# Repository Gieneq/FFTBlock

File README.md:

# FFTslice

Module to evaluate FFT. Communication with SPI. PGA for gain control. 2 selectable channels, additional DAC channel for selftest.

## DAC samples generation

See [notebook](Doc/DAC_samples/FFTSlice_DAC.ipynb) with all calculations. 

Frequencies from 20 Hz to 20 kHz are splitted into 100 ranges in logspace to better fit sound perception. 

3 variables affects output DAC frequency:
- constant TIM1 clock = 64 MHz,
- variable divider
- samples count

Divider can be freely changed, but samples count have to be generated in advance and stored in FLASH. There are 6 samples counts: 64, 128, 256, 512, 1024 and 2048. Higher samples counts fits better to generate low frequencies, lower samples counts are better fot higher frequencies.

100 parameters are calculated so that samples count and divider lowers time in which output voltage remain the same, and deviation from theoretical frequency is acceptable.

Resulting error remains below 1% as seen in the plot:

Matching of samples counts is more or less proportional:

Resulting frequencies are very close to theoretically calculated. In the plot sinewave with output buffer enabled without low pass filter:

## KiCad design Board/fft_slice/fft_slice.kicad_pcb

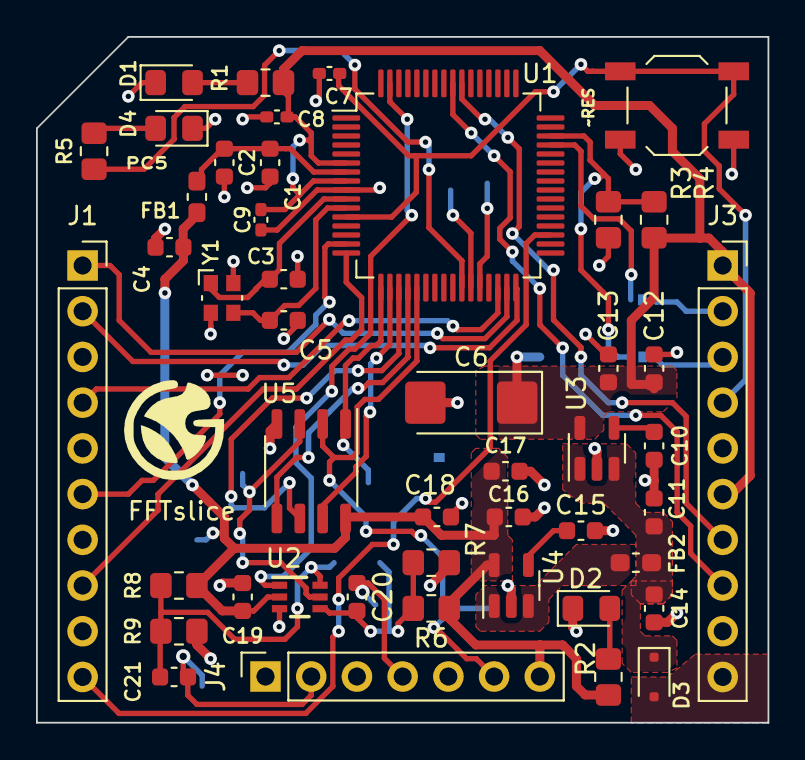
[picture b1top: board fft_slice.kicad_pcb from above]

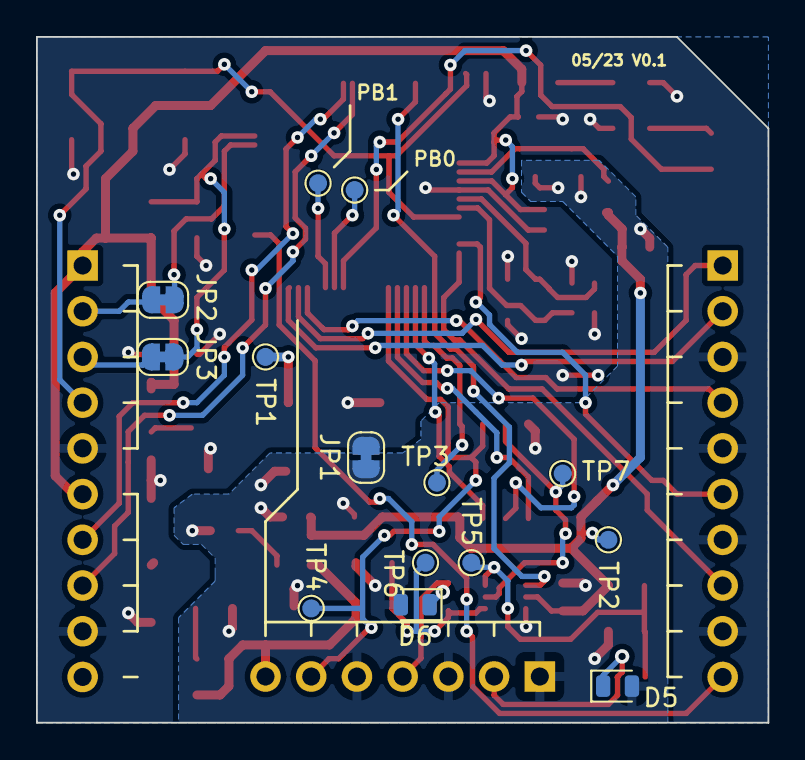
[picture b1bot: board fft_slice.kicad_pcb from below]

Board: 2 copper layers, 40.6 x 38.1 mm, 60 parts (14 on the bottom side), 42 nets.

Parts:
C1, C10, C15, C19: 10nF; C_0603_1608Metric
C2, C13, C14, C17, C20, C21: 1uF; C_0603_1608Metric
C3, C5: 10pF; C_0603_1608Metric
C4, C11, C12, C16, C18: 100nF; C_0603_1608Metric
C6: 100uF; CP_EIA-6032-15_Kemet-U_Pad2.25x2.35mm_HandSolder
C7, C8, C9: 100nF; C_0402_1005Metric_Pad0.74x0.62mm_HandSolder
D1, D2, D4: LED; LED_0805_2012Metric_Pad1.15x1.40mm_HandSolder
D3: PMEG2005EJ; D_SOD-323F
D5, D6: BZM55C3V3; D_MicroMELF
FB1, FB2: 120R@100MHz; L_0603_1608Metric_Pad1.05x0.95mm_HandSolder
J1, J3: Conn_01x10; PinSocket_1x10_P2.54mm_Vertical
J4: Conn_01x07; PinSocket_1x07_P2.54mm_Vertical
JP1, JP2, JP3: SolderJumper-2_P1.3mm_Bridged_RoundedPad1.0x1.5mm
R1, R2, R3, R5: 4k7; R_0805_2012Metric_Pad1.20x1.40mm_HandSolder
R4: NA; R_0805_2012Metric_Pad1.20x1.40mm_HandSolder
R6, R7, R8, R9: 100k; R_0805_2012Metric_Pad1.20x1.40mm_HandSolder
SW1: RESET; SW_SPST_TL3342
TP1, TP2, TP3, TP4, TP5, TP6, TP7, TP8, TP9: TestPoint; TestPoint_Pad_D1.0mm
U1: STM32G081RBTx; LQFP-64_10x10mm_P0.5mm
U2: TS5A9411DCKR; DCK0006A_N
U3, U4: SPX3819M5-L-3-3; SOT-23-5
U5: MCP6S22-I_MS; SOP-8_3.9x4.9mm_P1.27mm
Y1: 16MHz 10pF; Crystal_SMD_Abracon_ABM10-4Pin_2.5x2.0mm

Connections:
+3.3V: C6.1, C8.1, C9.1, C12.1, C13.1, J3.1, J3.6, R1.2, R4.1, TP1.1, U1.6 (VBAT), U1.8 (VDD), U3.5 (OUT)
+3.3VA: C4.1, C16.1, C17.1, C18.1, C19.1, FB1.1, J4.7, R2.2, R6.1, R8.1, TP2.1, U2.2 (V+), U4.5 (OUT), U5.8 (VDD)
+5V: D3.2 (A), J3.10
/Analog/EXTRN_SIG_SELECTED: TP7.1, U2.5 (COM), U5.3 (CH1)
/MCU/BOOT0: JP3.1 (A), R3.1, R4.2, U1.46 (PA14)
/MCU/OSC_IN: C3.1, U1.10 (PF0), Y1.1
/MCU/OSC_OUT: C5.1, U1.11 (PF1), Y1.3
/Power_Supply/5V SAFE: C11.1, C14.1, D3.1 (K), FB2.2, U3.1 (IN), U3.3 (EN)
/Power_Supply/5V_SAFE_FB: FB2.1, U4.1 (IN), U4.3 (EN)
ADC_SIG: TP3.1, U1.17 (PA0), U5.1 (VOUT)
DAC_SIG: J4.6, TP4.1, U1.21 (PA4), U5.2 (CH0)
DEV_MISO: J1.6, U1.15 (PC2)
DEV_MOSI: J1.8, U1.16 (PC3)
DEV_N_CS: J1.10, U1.35 (PB15)
DEV_N_INT: J1.2, U1.32 (PB12)
DEV_R_NW: J1.1, U1.31 (PB11)
DEV_SCK: J1.4, U1.30 (PB10)
EXTRN_SIG_1: C20.1, D6.1 (K), J4.4
EXTRN_SIG_2: C21.1, D5.1 (K), J4.2
EXTRN_SIG_SEL: U1.63 (PB9), U2.1 (IN)
GND: C3.2, C5.2, C6.2, C7.2, C8.2, C9.2, C10.2, C11.2, C12.2, C13.2, C14.2, D1.1 (K), D4.1 (K), J1.3, J1.5, J1.7, J1.9, J3.5, J3.9, JP1.1 (A), R3.2, SW1.2, U1.9 (VSS), U3.2 (GND), Y1.2, Y1.4
GNDA: C1.2, C2.2, C4.2, C15.2, C16.2, C17.2, C18.2, C19.2, D2.1 (K), D5.2 (A), D6.2 (A), J4.1, J4.3, J4.5, JP1.2 (B), R7.2, R9.2, U2.3 (GND), U4.2 (GND), U5.4 (VSS)
NRST: C7.1, J3.4, SW1.1, U1.12 (PF2)
unnamed: D1.2 (A), R1.1
unnamed: D2.2 (A), R2.1
unnamed: D4.2 (A), R5.2
unnamed: JP2.1 (A), U1.45 (PA13)
unnamed: TP8.1, U1.27 (PB0)
unnamed: TP9.1, U1.28 (PB1)
unnamed: R5.1, U1.26 (PC5)
unnamed: C1.1, C2.1, FB1.2, U1.7 (VREF+)
unnamed: C20.2, R6.2, R7.1, TP6.1, U2.4 (NC)
unnamed: C21.2, R8.2, R9.1, TP5.1, U2.6 (NO)
unnamed: C10.1, U3.4 (BP)
unnamed: C15.1, U4.4 (BP)
PGA_MOSI: U1.19 (PA2), U5.6 (SI)
PGA_N_CS: U1.20 (PA3), U5.5 (~CS)
PGA_SCK: U1.18 (PA1), U5.7 (SCK)
SWDCLK: J3.3, JP3.2 (B)
SWDIO: J3.2, JP2.2 (B)
UART2_RX: J3.8, U1.56 (PD6)
UART2_TX: J3.7, U1.55 (PD5)

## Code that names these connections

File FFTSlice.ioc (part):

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Mcu.Name=STM32G081RBTx
Mcu.Package=LQFP64
Mcu.UserName=STM32G081RBTx
PA0.Mode=IN0
PA0.Signal=ADC1_IN0
PA1.Mode=TX_Only_Simplex_Unidirect_Master
PA1.Signal=SPI1_SCK
PA13.Mode=Serial_Wire
PA13.Signal=SYS_SWDIO
PA14-BOOT0.Mode=Serial_Wire
PA14-BOOT0.Signal=SYS_SWCLK
PA2.Mode=TX_Only_Simplex_Unidirect_Master
PA2.Signal=SPI1_MOSI
PA3.GPIOParameters=GPIO_Speed,PinState,GPIO_Label
PA3.GPIO_Label=PGA_N_CS
PA3.GPIO_Speed=GPIO_SPEED_FREQ_VERY_HIGH
PA3.PinState=GPIO_PIN_SET
PA3.Signal=GPIO_Output
PA4.Signal=COMP_DAC11_group
PB10.Mode=Full_Duplex_Slave
PB10.Signal=SPI2_SCK
PB15.GPIOParameters=GPIO_PuPd,GPIO_Label
PB15.GPIO_Label=DEV_N_CS
PB15.GPIO_PuPd=GPIO_PULLUP
PB15.Signal=GPXTI15
PB9.GPIOParameters=GPIO_Speed,GPIO_Label
PB9.GPIO_Label=EXT_SIG_SELECT
PB9.GPIO_Speed=GPIO_SPEED_FREQ_VERY_HIGH
PB9.Signal=GPIO_Output
PC2.Mode=Full_Duplex_Slave
PC2.Signal=SPI2_MISO
PC3.Mode=Full_Duplex_Slave
PC3.Signal=SPI2_MOSI
PC5.GPIOParameters=GPIO_Label
PC5.GPIO_Label=LED
PC5.Signal=GPIO_Output
PD5.Mode=Asynchronous
PD5.Signal=USART2_TX
PD6.Mode=Asynchronous
PD6.Signal=USART2_RX
PF0-OSC_IN\ (PF0).Mode=HSE-External-Oscillator
PF0-OSC_IN\ (PF0).Signal=RCC_OSC_IN
PF1-OSC_OUT\ (PF1).Mode=HSE-External-Oscillator
PF1-OSC_OUT\ (PF1).Signal=RCC_OSC_OUT
RCC.HSE_VALUE=25000000
RCC.SYSCLKFreq_VALUE=64000000
RCC.SYSCLKSource=RCC_SYSCLKSOURCE_PLLCLK
board=custom

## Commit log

2023-05-28 Working, DAC not - try
2023-05-28 MCP6S22 component driver
2023-05-29 Channel selector
2023-05-29 Device driver initial
2023-06-01 Signal generator DAC introduced
2023-06-05 Folders rework, add timer calculations
2023-07-31 Working sine generation
2023-08-01 Working DAC samples
